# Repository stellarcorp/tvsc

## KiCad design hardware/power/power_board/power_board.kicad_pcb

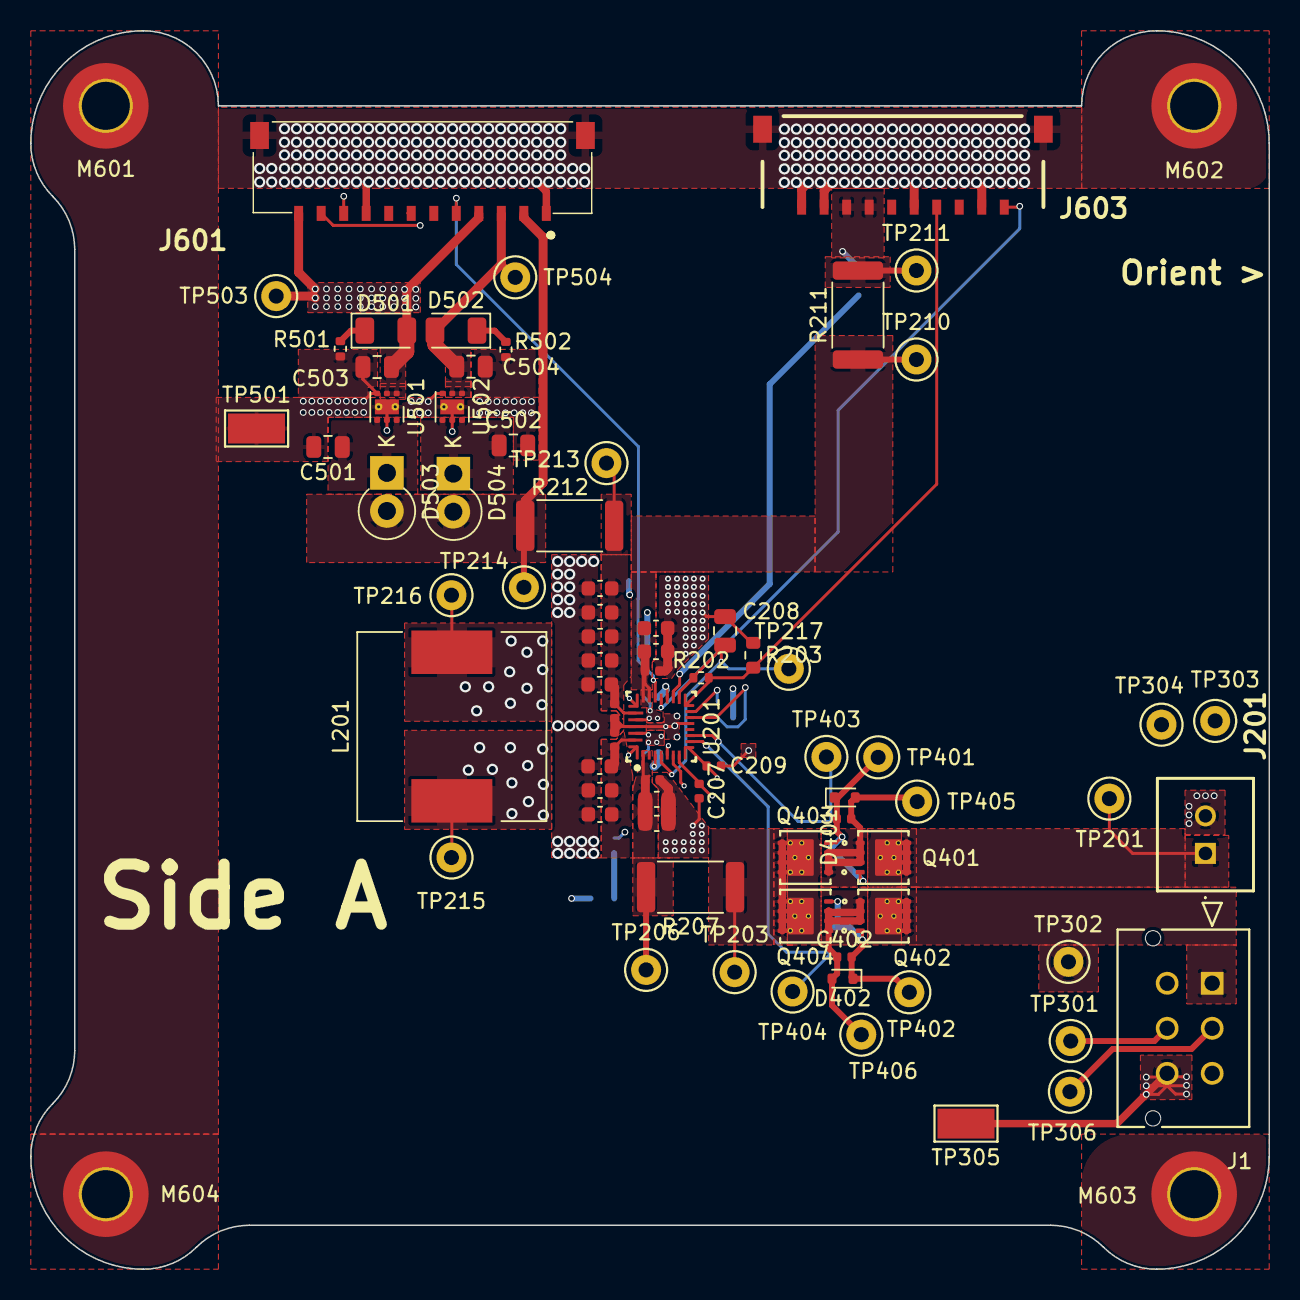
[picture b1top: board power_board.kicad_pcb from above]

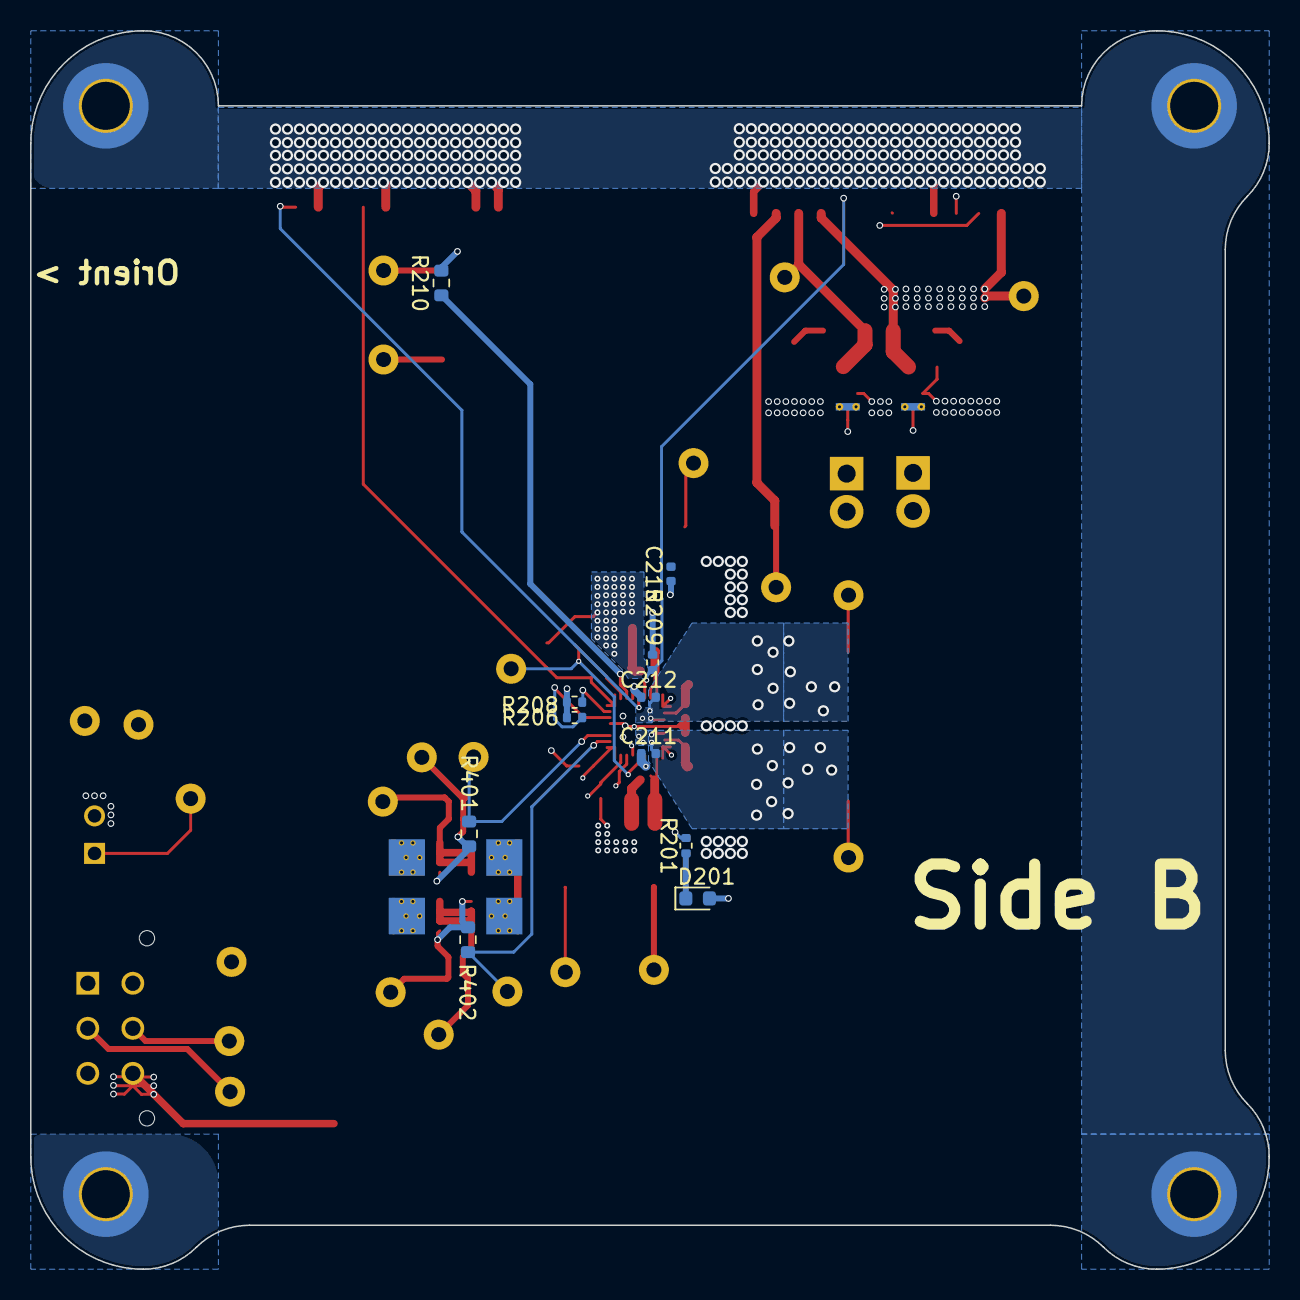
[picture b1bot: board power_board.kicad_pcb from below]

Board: 4 copper layers, 82.5 x 82.5 mm, 90 parts (11 on the bottom side), 40 nets.

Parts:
C201, C202, C203, C205, C206, C214, C216, C217, C218, C219, C220, C221: 10u; C_0603_1608Metric
C204, C207, C209, C210, C213, C222: 0.1u; C_0402_1005Metric
C208: 4.7u; C_0805_2012Metric
C211, C212: 0.047u; C_0402_1005Metric
C215, C401, C402: 1n; C_0402_1005Metric
C501, C502: 1u; C_0805_2012Metric
C503, C504: 2.2u; C_0805_2012Metric
D201: Green LED; LED_0603_1608Metric
D401, D402: 12V; D_SOD-523
D501, D502: White LED; LED_1206_3216Metric
D503, D504: 3A; D_DO-15_P2.54mm_Vertical_KathodeUp
J1: Molex_430450612
J201: B02B-XASK-1 (LF)(SN); B02BXASK1LFSN
J601: 504050-1291; 5040501291
J603: 504050-1091
L201: 1uH; L_12x12mm_H8mm
M601, M602, M603, M604: MountingHole_3.2mm_M3_ISO7380_Pad_TopBottom
Q401, Q402, Q403, Q404: CSD17581Q3A; Q3A_TEX
R201: 2.21k; R_0402_1005Metric
R202: 5.24k; R_0402_1005Metric
R203: 30.31k; R_0603_1608Metric
R206, R208, R209: 10k; R_0402_1005Metric
R207, R211, R212: 0.01; R_2512_6332Metric
R210: 100; R_0603_1608Metric
R401, R402: 294; R_0603_1608Metric
R501: 68; R_0402_1005Metric
R502: 150; R_0402_1005Metric
TP201, TP203, TP206, TP210, TP211, TP213, TP214, TP215, TP216, TP217, TP303, TP304, TP405, TP406: White; TestPoint_Keystone_5000-5004_Miniature
TP301, TP306, TP403, TP404: Black; TestPoint_Keystone_5000-5004_Miniature
TP302, TP401, TP402, TP503, TP504: Red; TestPoint_Keystone_5000-5004_Miniature
TP305, TP501: Ring; TestPoint_Keystone_5019_Minature
U201: BQ25798RQMR; RQM0029A-MFG
U501: TLV76733DRVx; WSON-6-1EP_2x2mm_P0.65mm_EP1x1.6mm_ThermalVias
U502: TLV76750DRVx; WSON-6-1EP_2x2mm_P0.65mm_EP1x1.6mm_ThermalVias

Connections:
+3.3V: C503.1, D201.2 (A), D501.2 (A), J601.4, J601.12, R206.1, R208.1, R209.1, TP503.1, U501.1 (OUT), U501.2 (SNS)
+5V: C504.1, D502.2 (A), J601.3, TP504.1, U502.1 (OUT), U502.2 (SNS)
/Charger/BAT: C216.1, C218.1, C222.1, R211.1, TP210.1, U201.22 (BAT), U201.23 (BAT)
/Charger/BATP: R210.1, U201.18 (BATP)
/Charger/BTST1: C211.1, U201.4 (BTST1)
/Charger/BTST2: C212.1, U201.19 (BTST2)
/Charger/PMID: C201.1, C202.1, C203.1, C204.1, U201.29 (PMID)
/Charger/REGN: C208.1, R202.1, TP217.1, U201.5 (REGN), U201.17 (ILIM_HIZ)
/Charger/STAT: R201.2, U201.1 (STAT)
/Charger/SW1: C211.2, L201.1, TP215.1, U201.28 (SW1)
/Charger/SW2: C212.2, L201.2, TP216.1, U201.26 (SW2)
/Charger/SYS: C213.1, C214.1, C217.1, C219.1, C220.1, C221.1, R212.1, TP213.1, U201.25 (SYS)
/Charger/VBUS_PIN: C205.1, C206.1, C210.1, R207.2, TP206.1, U201.2 (VBUS), U201.3 (VBUS)
/Input Selection/ACDRV1_SOURCE: C401.1, D401.2 (A), Q401.1 (S), Q403.1 (S), TP405.1
/Input Selection/ACDRV2_SOURCE: C402.1, D402.2 (A), Q402.1 (S), Q404.1 (S), TP406.1
/Input Selection/SOLAR_VBUS_GATE: C401.2, D401.1 (K), Q401.4 (G), Q403.4 (G), R401.1, TP401.1
/Input Selection/USB_VBUS_GATE: C402.2, D402.1 (K), Q402.4 (G), Q404.4 (G), R402.1, TP402.1
/USB/USB_CC1: J1.2, TP306.1
/USB/USB_CC2: J1.5, TP301.1
ACDRV1: R401.2, TP403.1, U201.11 (ACDRV1)
ACDRV2: R402.2, TP404.1, U201.10 (ACDRV2)
BATTERY_+: J603.3, J603.4, R210.2, R211.2, TP211.1
BATTERY_ID: J603.10, U201.20 (PROG)
CHARGER_INT: J601.5, R209.2, U201.21 (INT_N)
GND: C201.2, C202.2, C203.2, C204.2, C205.2, C206.2, C207.2, C208.2, C209.2, C210.2, C213.2, C214.2, C215.2, C216.2, C217.2, C218.2, C219.2, C220.2, C221.2, C222.2, C501.2, C502.2, C503.2, C504.2, J1.6, J201.2, J601.1, J601.6, J601.9, J601.MP1, J601.MP2, J603.1, J603.2, J603.6, J603.9, J603.11 (MP1), J603.12 (MP2), M601.1 (Hole), M602.1 (Hole), M603.1 (Hole), M604.1 (Hole), R203.2, R501.2, R502.2, TP305.1, TP501.1, U201.13 (CE_N), U201.27 (GND), U501.3 (GND), U501.5 (GND), U501.7 (PAD), U502.3 (GND), U502.5 (GND), U502.7 (PAD)
unnamed: D201.1 (K), R201.1
unnamed: D501.1 (K), R501.1
unnamed: D502.1 (K), R502.1
unnamed: C501.1, D503.1 (K), U501.4 (EN), U501.6 (IN)
unnamed: C502.1, D504.1 (K), U502.4 (EN), U502.6 (IN)
unnamed: C215.1, U201.24 (SDRV)
POWER_SCL: J601.11, R206.2, U201.14 (SCL)
POWER_SDA: J601.10, R208.2, U201.15 (SDA)
SOLAR_VBUS: C209.1, J201.1, Q401.5 (D), TP201.1, U201.9 (VAC1)
THERMISTOR: J603.7, R202.2, R203.1, U201.16 (TS)
USB_D+: J1.3, TP303.1, U201.6 (D+)
USB_D-: J1.4, TP304.1, U201.7 (D-)
USB_VBUS: C207.1, J1.1, Q402.5 (D), TP302.1, U201.8 (VAC2)
VBUS: Q403.5 (D), Q404.5 (D), R207.1, TP203.1
VCC: D503.2 (A), D504.2 (A), J601.2, R212.2, TP214.1
